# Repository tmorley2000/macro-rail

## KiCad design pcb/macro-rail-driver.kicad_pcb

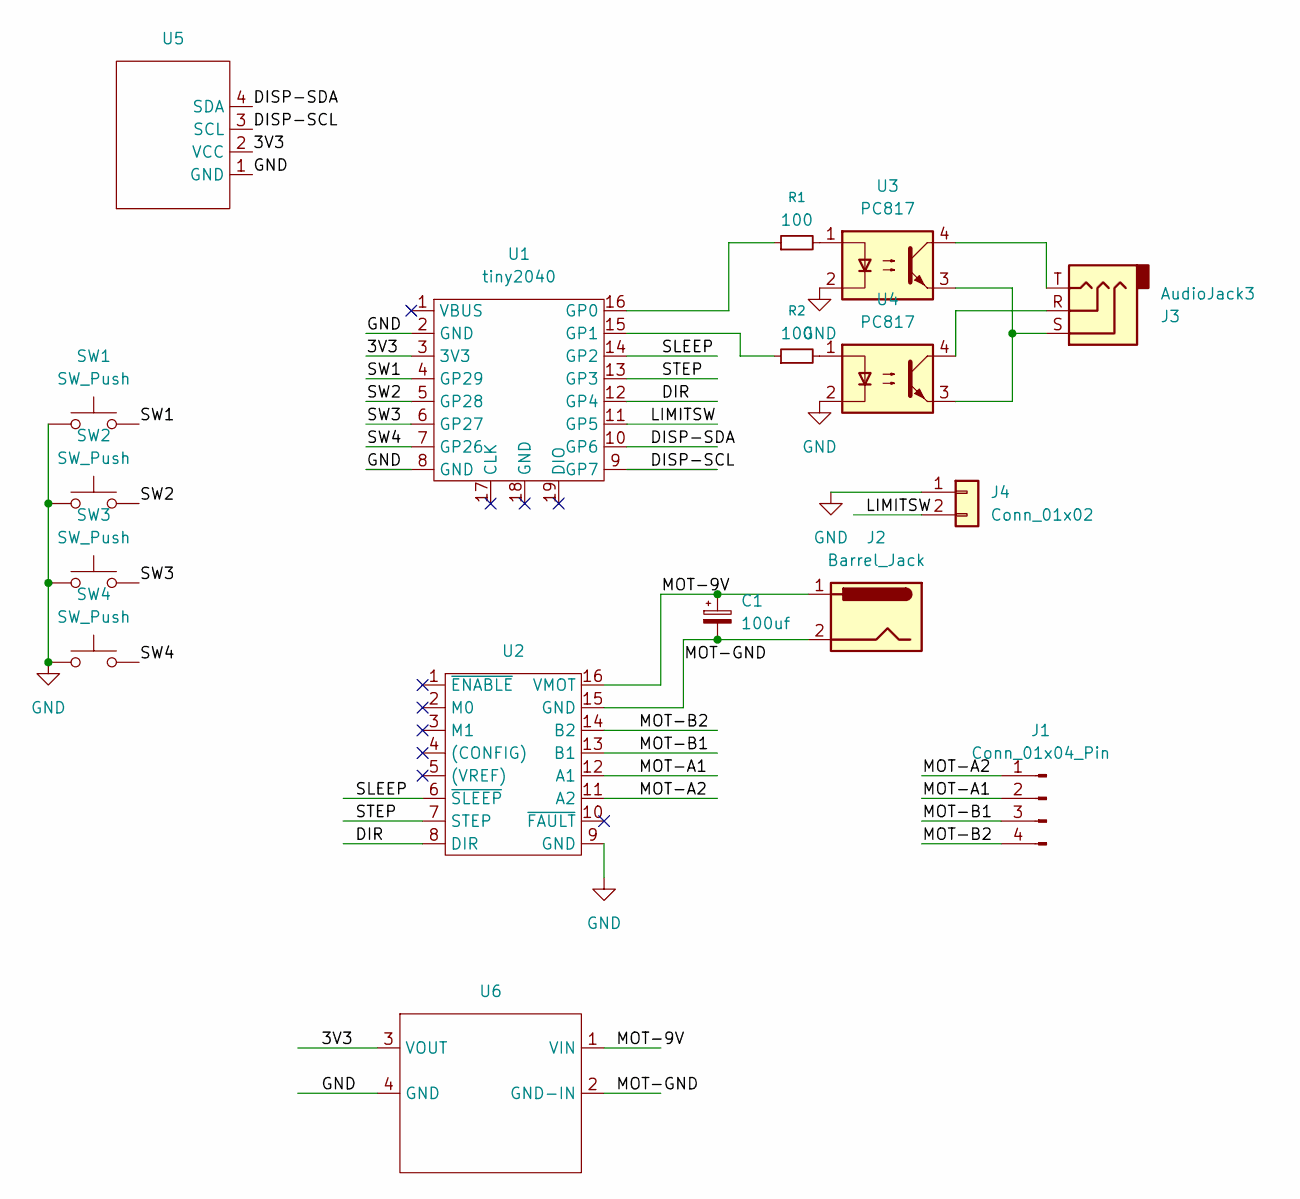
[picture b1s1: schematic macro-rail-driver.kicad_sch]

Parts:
C1: 100uf; CP_Radial_D5.0mm_P2.50mm
J1: Conn_01x04_Pin; PinHeader_1x04_P2.54mm_Horizontal
J2: Barrel_Jack; PinHeader_1x02_P2.54mm_Vertical
J3: AudioJack3; Jack_3.5mm_CUI_SJ1-3525N_Horizontal
J4: Conn_01x02; PinHeader_1x02_P2.54mm_Horizontal
R1, R2: 100; R_Axial_DIN0207_L6.3mm_D2.5mm_P7.62mm_Horizontal
SW1, SW2, SW3, SW4: SW_Push; SW_PUSH_6mm_H5mm_Jumpered_Connections
U1: tiny2040
U2: Pololu-DRV8834
U3, U4: PC817; DIP-4_W7.62mm
U5: PiHut 1.3in OLED 128x64
U6: MP1534_HW1333ABC_DC-DC_Converter

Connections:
/3V3: U1.3 (3V3), U5.2 (VCC), U6.3 (VOUT)
/DIR: U1.12 (GP4), U2.8 (DIR)
/DISP-SCL: U1.9 (GP7), U5.3 (SCL)
/DISP-SDA: U1.10 (GP6), U5.4 (SDA)
/LIMITSW: J4.2, U1.11 (GP5)
/MOT-9V: C1.1, J2.1, U2.16 (VMOT), U6.1 (VIN)
/MOT-A1: J1.2, U2.12 (A1)
/MOT-A2: J1.1, U2.11 (A2)
/MOT-B1: J1.3, U2.13 (B1)
/MOT-B2: J1.4, U2.14 (B2)
/MOT-GND: C1.2, J2.2, U2.15 (GND), U6.2 (GND-IN)
/SLEEP: U1.14 (GP2), U2.6 (~SLEEP)
/STEP: U1.13 (GP3), U2.7 (STEP)
/SW1: SW1.2, U1.4 (GP29)
/SW2: SW2.2, U1.5 (GP28)
/SW3: SW3.2, U1.6 (GP27)
/SW4: SW4.2, U1.7 (GP26)
GND: J4.1, SW1.1, SW2.1, SW3.1, SW4.1, U1.2 (GND), U1.8 (GND), U2.9 (GND), U3.2, U4.2, U5.1 (GND), U6.4 (GND)
unnamed: J3.R, U4.4
unnamed: J3.S, U3.3, U4.3
unnamed: J3.T, U3.4
unnamed: R1.2, U3.1
unnamed: R2.2, U4.1
unnamed: R1.1, U1.16 (GP0)
unnamed: R2.1, U1.15 (GP1)

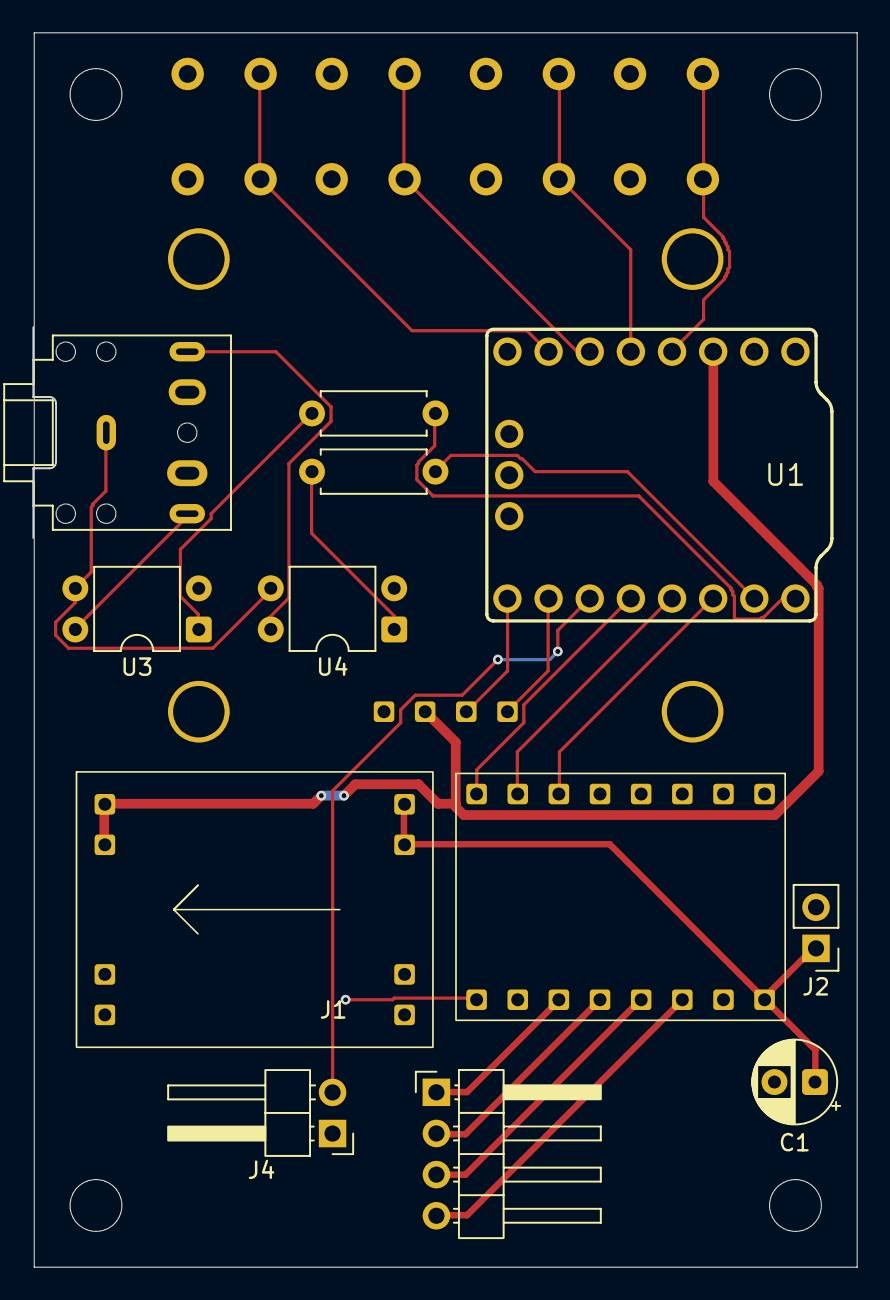
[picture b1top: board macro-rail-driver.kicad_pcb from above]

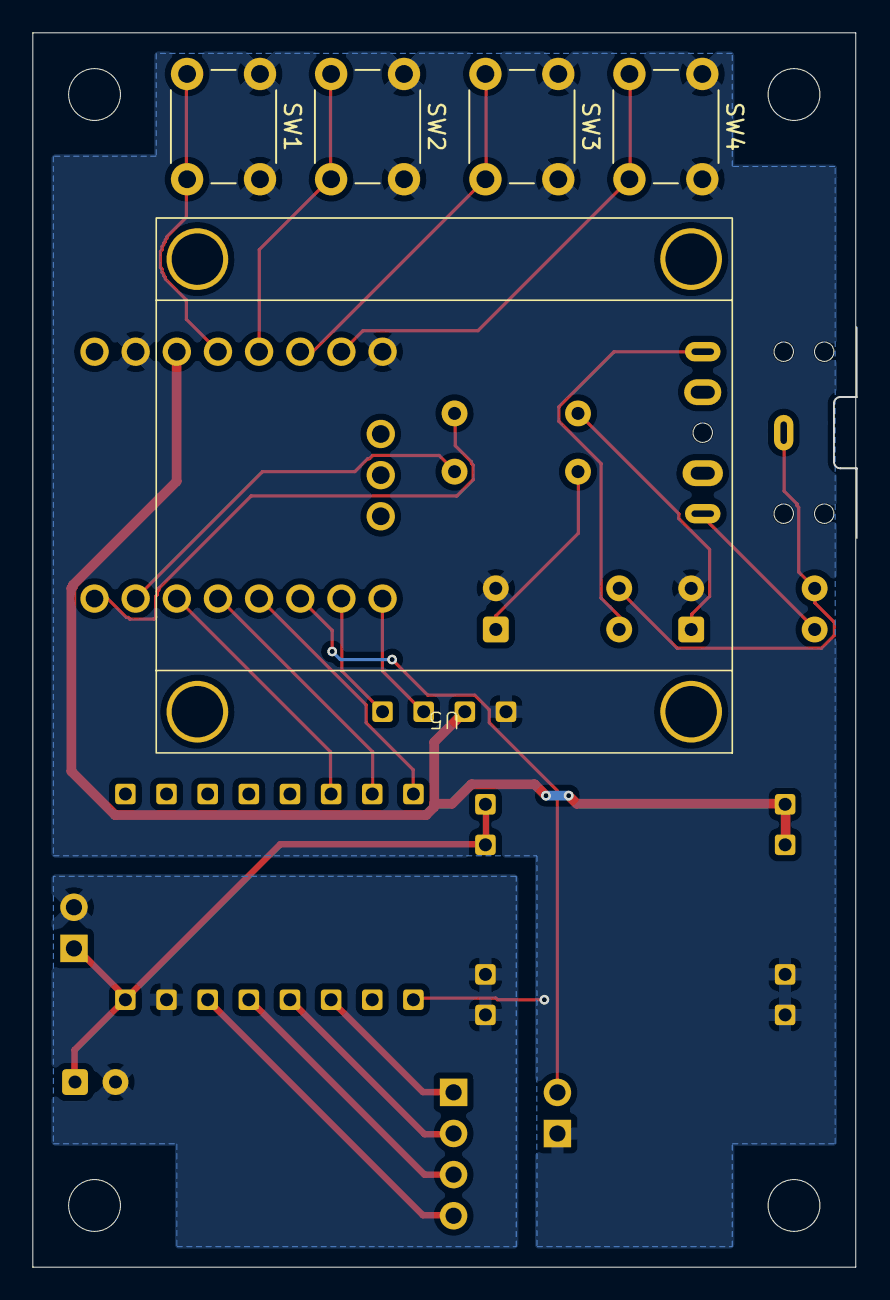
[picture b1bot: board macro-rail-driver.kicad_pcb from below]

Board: 2 copper layers, 50.8 x 76.2 mm, 17 parts (5 on the bottom side), 25 nets.
